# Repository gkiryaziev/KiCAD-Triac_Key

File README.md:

## KiCAD-Triac_Key

[KiCAD](http://kicad-pcb.org/) [MOC3063M](http://www.onsemi.com/pub/Collateral/MOC3163M-D.pdf) Triac Driver and [BT138](https://www.nxp.com/docs/en/data-sheet/BF245A-B-C.pdf) Triac Key

### Info
```
This triac key was designed for MOC3063M triac driver and BT138 triac and for other pin-to-pin compatible.
This is an early version of the board and is distributed as is.
The missing 3D models you can find on open resources on the Internet.
```

#### License
```
CC BY 4.0
```

### Screenshot

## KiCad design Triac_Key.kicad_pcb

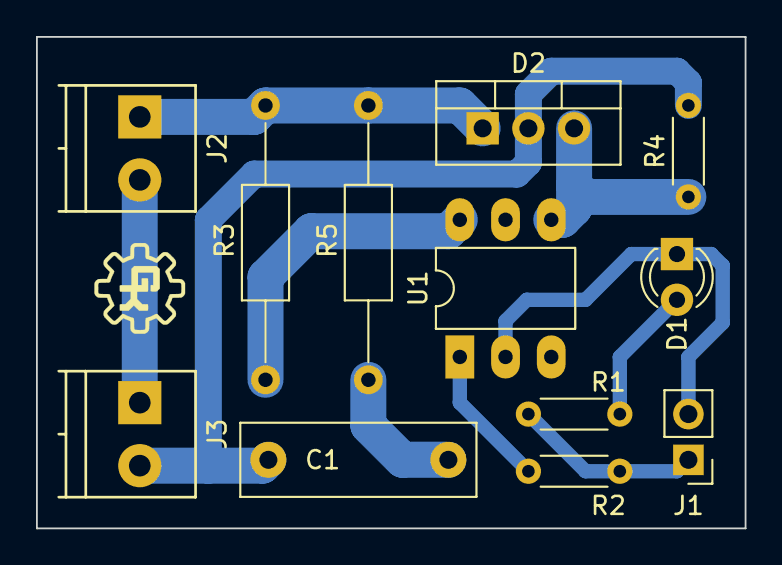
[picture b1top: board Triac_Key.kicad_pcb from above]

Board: 2 copper layers, 39.4 x 27.3 mm, 12 parts (0 on the bottom side), 10 nets.

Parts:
C1: 10nF 400V; C_Rect_L13.0mm_W4.0mm_P10.00mm_FKS3_FKP3_MKS4
D1: LED SIGNAL; LED_D3.0mm
D2: BT138; TO-220-3_Vertical
J1: Signal; Pin_Header_Straight_1x02_Pitch2.54mm
J2: Load; TerminalBlock_Phoenix_PT-3.5mm_2pol
J3: 220v; TerminalBlock_Phoenix_PT-3.5mm_2pol
R1, R2: 220; R_Axial_DIN0204_L3.6mm_D1.6mm_P5.08mm_Horizontal
R3: 360 1W; R_Axial_DIN0207_L6.3mm_D2.5mm_P15.24mm_Horizontal
R4: 360; R_Axial_DIN0204_L3.6mm_D1.6mm_P5.08mm_Horizontal
R5: 39 1W; R_Axial_DIN0207_L6.3mm_D2.5mm_P15.24mm_Horizontal
U1: MOC3063M; DIP-6_W7.62mm_LongPads

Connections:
GND: D1.1, J1.2, U1.2
unnamed: C1.1, R5.1
unnamed: C1.2, D2.2, J3.2, R4.2
unnamed: D1.2, R1.2
unnamed: D2.1, J2.1, R3.1, R5.2
unnamed: D2.3, R4.1, U1.4
unnamed: J1.1, R1.1, R2.2
unnamed: J2.2, J3.1
unnamed: R2.1, U1.1
unnamed: R3.2, U1.6
